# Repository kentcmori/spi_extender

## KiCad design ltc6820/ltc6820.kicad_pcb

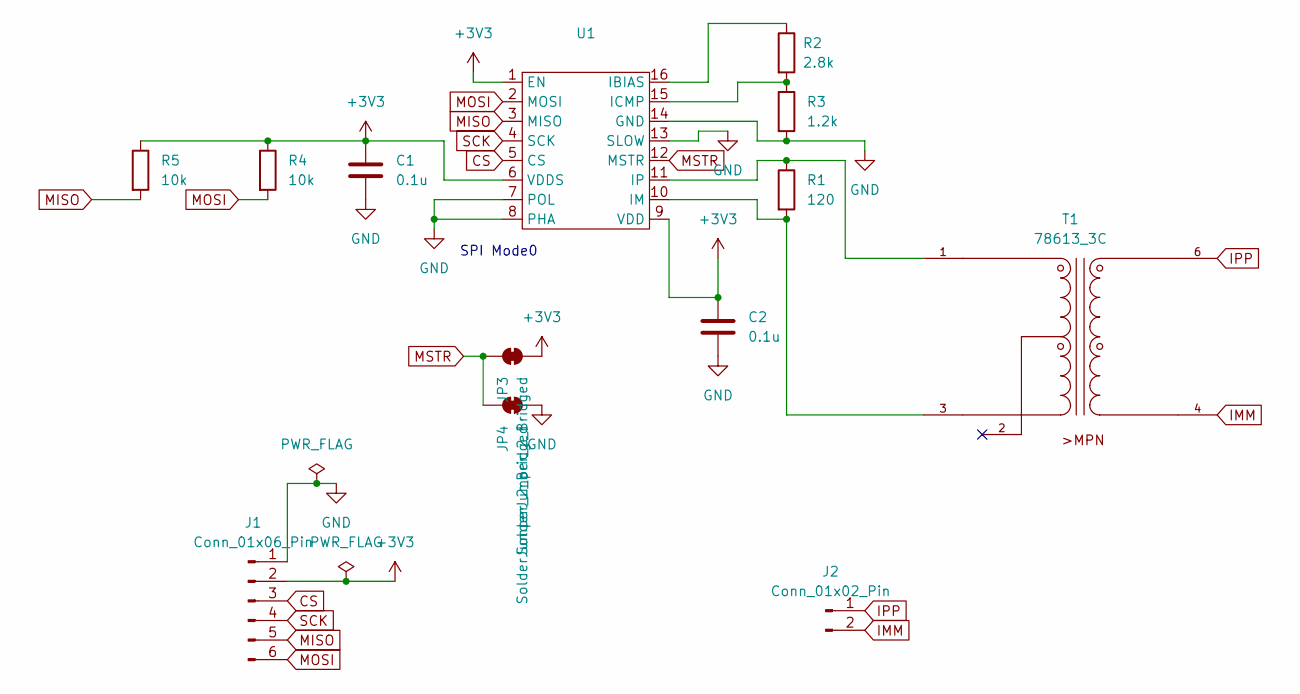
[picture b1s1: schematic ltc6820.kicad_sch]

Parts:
C1, C2: 0.1u; C_0603_1608Metric
J1: Conn_01x06_Pin; PinHeader_1x06_P2.54mm_Horizontal
J2: Conn_01x02_Pin; PinHeader_1x02_P2.54mm_Horizontal
JP3, JP4: SolderJumper_2_Bridged; SolderJumper-2_P1.3mm_Open_RoundedPad1.0x1.5mm
R1: 120; R_0603_1608Metric
R2: 2.8k; R_0603_1608Metric
R3: 1.2k; R_0603_1608Metric
R4, R5: 10k; R_Axial_DIN0207_L6.3mm_D2.5mm_P10.16mm_Horizontal
T1: 78613_3C
U1: MSOP-16_3x4.039mm_P0.5mm

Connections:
+3V3: C1.1, C2.1, J1.2, JP3.1 (A), R4.1, R5.1, U1.1 (EN), U1.6 (VDDS), U1.9 (VDD)
CS: J1.3, U1.5 (CS)
GND: C1.2, C2.2, J1.1, JP4.1 (A), R3.2, U1.7 (POL), U1.8 (PHA), U1.13 (SLOW), U1.14 (GND)
IMM: J2.2, T1.4
IPP: J2.1, T1.6
MISO: J1.5, R5.2, U1.3 (MISO)
MOSI: J1.6, R4.2, U1.2 (MOSI)
MSTR: JP3.2 (B), JP4.2 (B), U1.12 (MSTR)
unnamed: R2.1, U1.16 (IBIAS)
unnamed: R2.2, R3.1, U1.15 (ICMP)
unnamed: R1.2, T1.3, U1.10 (IM)
unnamed: R1.1, T1.1, U1.11 (IP)
SCK: J1.4, U1.4 (SCK)

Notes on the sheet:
SPI Mode0

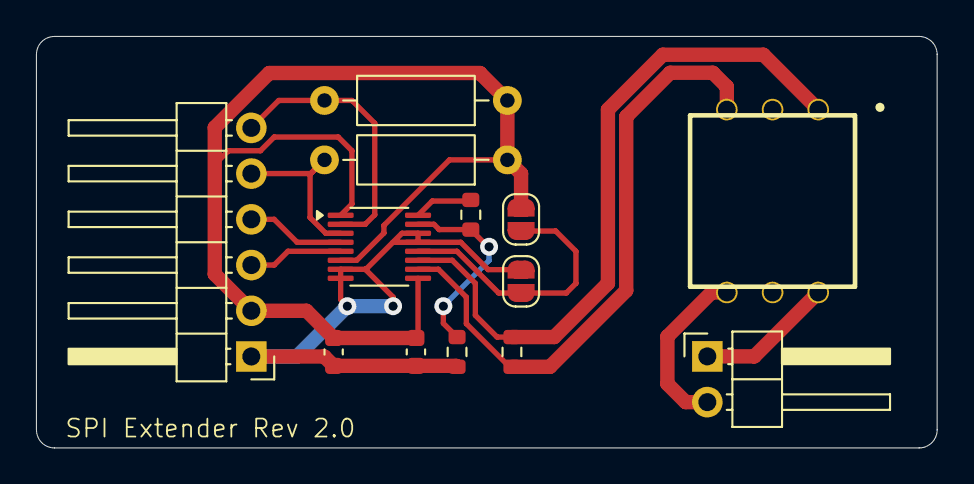
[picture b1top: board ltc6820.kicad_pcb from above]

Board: 2 copper layers, 50.0 x 22.9 mm, 13 parts (0 on the bottom side), 13 nets.

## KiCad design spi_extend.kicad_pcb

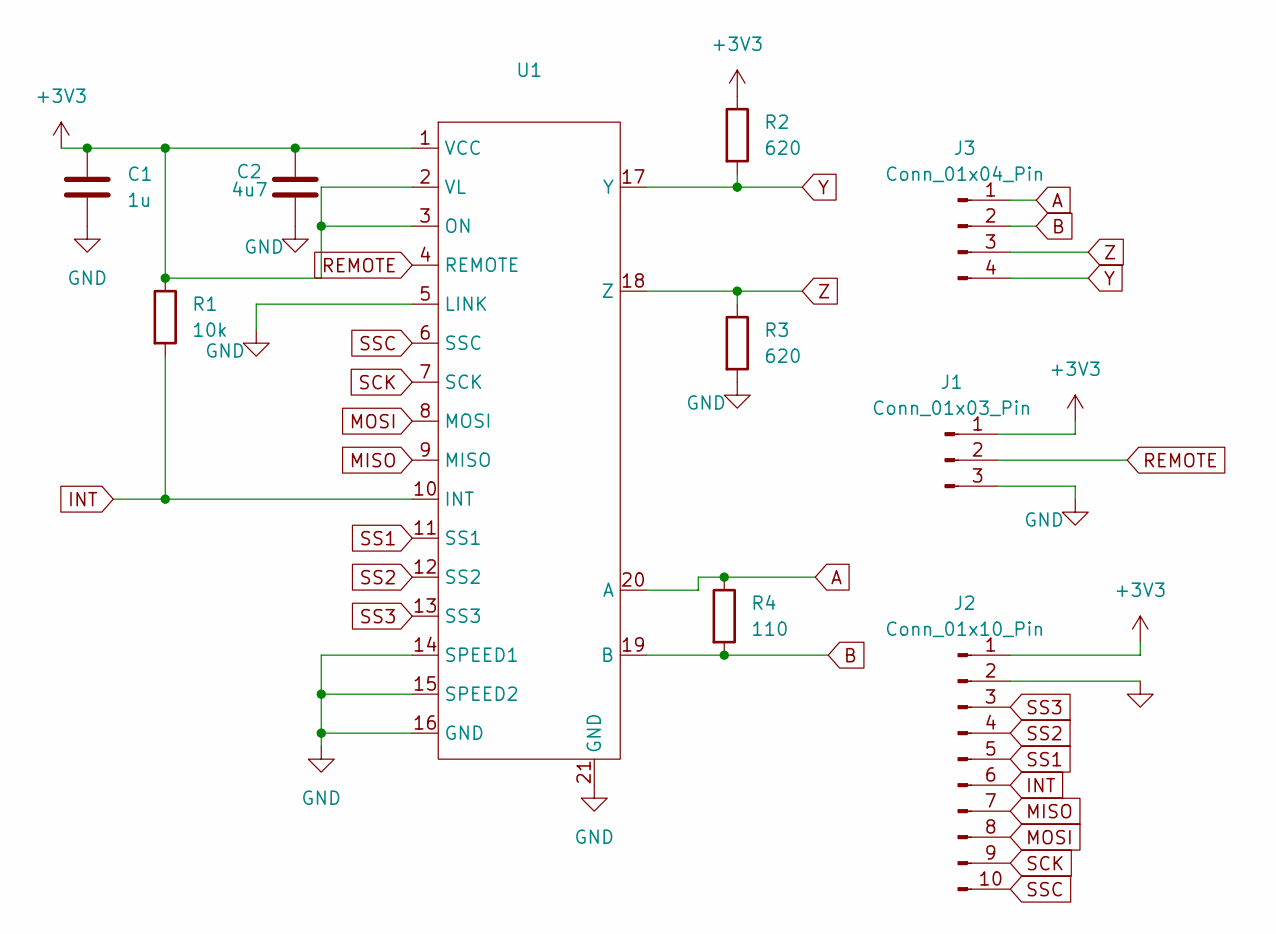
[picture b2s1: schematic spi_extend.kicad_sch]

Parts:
C1: 1u; C_0603_1608Metric
C2: 4u7; C_0603_1608Metric
J1: Conn_01x03_Pin; PinHeader_1x03_P2.54mm_Horizontal
J2: Conn_01x10_Pin; PinHeader_1x10_P2.54mm_Horizontal
J3: Conn_01x04_Pin; PinHeader_1x04_P2.54mm_Horizontal
R1: 10k; R_0603_1608Metric
R2, R3: 620; R_0603_1608Metric
R4: 110; R_0603_1608Metric
U1: QFN-20-1EP_4x5mm_P0.5mm_EP2.65x3.65mm

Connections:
+3V3: C1.1, C2.1, J1.1, J2.1, R1.1, R2.1, U1.1 (VCC), U1.2 (VL), U1.3 (ON)
A: J3.1, R4.1, U1.20 (A)
B: J3.2, R4.2, U1.19 (B)
GND: C1.2, C2.2, J1.3, J2.2, R3.2, U1.5 (LINK), U1.14 (SPEED1), U1.15 (SPEED2), U1.16 (GND), U1.21 (GND)
INT: J2.6, R1.2, U1.10 (INT)
MISO: J2.7, U1.9 (MISO)
MOSI: J2.8, U1.8 (MOSI)
REMOTE: J1.2, U1.4 (REMOTE)
SCK: J2.9, U1.7 (SCK)
SS1: J2.5, U1.11 (SS1)
SS2: J2.4, U1.12 (SS2)
SS3: J2.3, U1.13 (SS3)
SSC: J2.10, U1.6 (SSC)
Y: J3.4, R2.2, U1.17 (Y)
Z: J3.3, R3.1, U1.18 (Z)

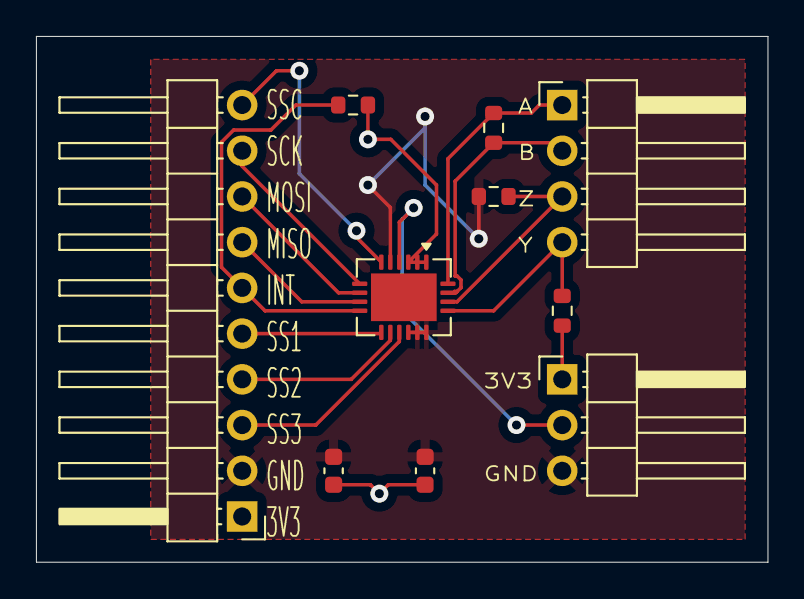
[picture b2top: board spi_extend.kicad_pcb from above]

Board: 2 copper layers, 40.6 x 29.2 mm, 10 parts (0 on the bottom side), 15 nets.

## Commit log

2025-11-27 Add LTC 6820
2025-12-14 Update: SPI Extender
2025-12-14 GERBER
